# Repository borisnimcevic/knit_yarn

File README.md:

# Knit & Yarn Badge

A round PCB badge shaped like a ball of yarn with knitting needles. Six LEDs shine through the board face-down, lighting up the design from behind. Powered by a CR2032 coin cell; the brooch pin doubles as the power switch.

Designed in KiCad. Three badge variants and one SAO variant are included.

---

## Versions

| Folder | Description |
|--------|-------------|
| `knit_yarn_badge_v1` | First prototype — through-hole battery holder |
| `knit_yarn_badge_v2` | SMD redesign, improved layout |
| `knit_yarn_badge_v3` | Current version — 0805 components, no vias |
| `knit_yarn_SAO` | Simple Add-On variant with 2×2 header |

---

## Bill of Materials (per badge)

| Reference | Component | Package | Qty |
|-----------|-----------|---------|-----|
| D1–D6 | LED (any color) | 0805 | 6 |
| R1–R6 | Resistor | 0805 | 6 |
| BT1 | CR2032 coin cell holder | THT | 1 |
| SW1 | Brooch pin / SPST switch | custom | 1 |

> **Note:** Resistor values depend on your LED choice. For a standard 2V LED with a 3V CR2032 at ~10 mA per LED: R = (3V − 2V) / 10 mA = **100 Ω**.

---

## Ordering

Ready-to-order Gerber zips are in the [`order/`](./order/) folder:

- [`order/knit_yarn_badge_v1.zip`](./order/knit_yarn_badge_v1.zip)
- [`order/knit_yarn_badge_v2.zip`](./order/knit_yarn_badge_v2.zip)
- [`order/knit_yarn_badge_v3.zip`](./order/knit_yarn_badge_v3.zip) ← recommended
- [`order/knit_yarn_SAO.zip`](./order/knit_yarn_SAO.zip)

Upload the zip directly to your PCB fab (JLCPCB, PCBWay, etc.).

---

## Assembly

1. **Resistors** — solder all 6 first (they're the lowest-profile component)
2. **LEDs** — place them **face down** (they shine into the PCB, not away from it)
   - The green mark on the LED points to the cathode, which aligns with the white edge on the footprint

3. **Battery holder** — battery inserts from the back
4. **Brooch pin** — two-part assembly; use enough solder on both pads or the tension from clipping it may pop it loose

---

## SVG Source Files

The artwork SVGs used to generate the board graphics live in [`svg_source/`](./svg_source/).

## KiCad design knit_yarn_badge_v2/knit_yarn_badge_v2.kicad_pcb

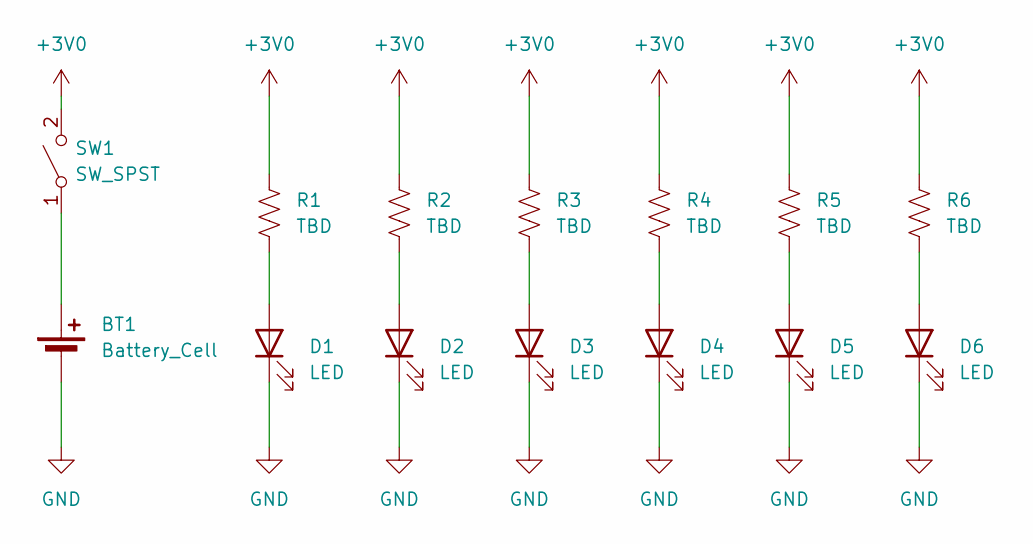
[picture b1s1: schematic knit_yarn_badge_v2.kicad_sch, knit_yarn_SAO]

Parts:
BT1: Battery_Cell; BatteryHolder_Keystone_3002_1x2032
D1, D2, D3, D4, D5, D6: LED; LED_0603_1608Metric_Pad1.05x0.95mm_HandSolder
R1, R2, R3, R4, R5, R6: TBD; R_0603_1608Metric_Pad0.98x0.95mm_HandSolder
SW1: SW_SPST; brooch_SW_20mm

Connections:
+3V0: R1.1, R2.1, R3.1, R4.1, R5.1, R6.1, SW1.2 (B)
GND: BT1.2 (-), D1.1 (K), D2.1 (K), D3.1 (K), D4.1 (K), D5.1 (K), D6.1 (K)
unnamed: BT1.1 (+), SW1.1 (A)
unnamed: D1.2 (A), R1.2
unnamed: D2.2 (A), R2.2
unnamed: D3.2 (A), R3.2
unnamed: D4.2 (A), R4.2
unnamed: D5.2 (A), R5.2
unnamed: D6.2 (A), R6.2

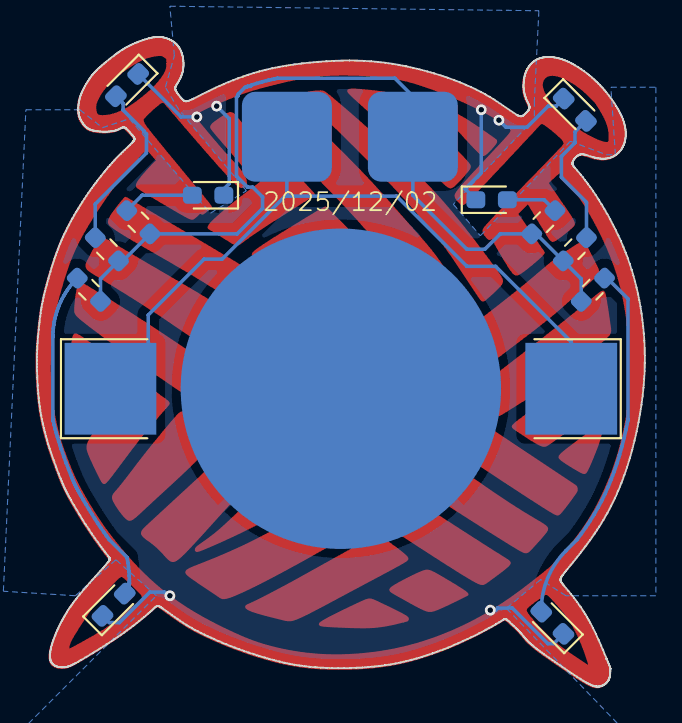
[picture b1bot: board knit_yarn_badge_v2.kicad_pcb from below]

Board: 2 copper layers, 33.8 x 36.1 mm, 14 parts (14 on the bottom side), 9 nets.

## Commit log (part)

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2025-05-12 Init repo.
2025-05-12 happy with graphics and added two more LEDs
2025-05-12 components in place
2025-05-12 back pour area
2025-05-12 fist draft
2025-05-12 one via
2025-05-12 add silk screen
2025-12-02 add inspo image
2025-12-02 move v1 pcb to it's own folder
2025-12-02 init v2 of the badge
2025-12-02 ignore lock files
2025-12-02 ignore backup files
2025-12-02 non movable components locked
2025-12-02 components arranged
2025-12-02 everything routed
2025-12-02 correct 3d model for the battery holder
2025-12-02 v2 ready for order
2025-12-03 init SAO version
2025-12-03 SAO connected and errors checked
2025-12-03 added the question
2025-12-04 generated gerbers
2025-12-04 v2 generated gerbers
2025-12-04 zipped gergers
2025-12-29 init instrucions
2025-12-29 add image
2025-12-29 improved instructions
2026-06-25 clean up the repo
2026-06-29 separate dir for svg sources
2026-06-29 all svg files in one place
2026-06-29 gerber for v3 ready
2026-06-29 removed incorrect data in the readme
